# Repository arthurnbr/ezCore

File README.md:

# ezCore — porte-clés compagnon MeshCore (V3, circulaire, UX)

Compagnon MeshCore ultra-compact en **disque Ø48 mm** (type AirTag) autour du
**Seeed XIAO nRF52840** + module LoRa **Wio-SX1262** (EU868) : appairage BLE sans
code, mise à jour OTA par application, **antenne NFC ronde intégrée**, **LED
bi-couleur** de retour utilisateur, **port de charge/flash magnétique 4 points**
(pogo), et batterie **1050 mAh** au dos du boîtier.

> État : schéma ERC 0/0, PCB placée UX + routée (Freerouting). Quelques points DRC
> à finir dans KiCad. Tout est reproductible via `hardware/tools/`.

## Disposition UX (V3)

Placement pensé usage, carte propre et symétrique :

- **Pogo magnétique `J5` en haut** (VBUS/GND/D+/D−, type chargeur de montre) :
  charge + flash UF2 + série USB.
- **Bouton `SW1` + LED bi-couleur `D1`/`D2` à gauche** (90° du pogo) : retour
  visuel type AirPods (rouge = charge, vert = prêt, orange = transition). Pilotée
  par D9 (rouge) / D8 (vert) du XIAO via `R1`/`R2` (série).
- **Ports de debug SWD `TP1-TP4` sous le bouton** (RST / SWDIO / SWCLK / GND).
- **Interrupteur ON/OFF `SW3` à droite** (coupe la batterie).
- **XIAO `U1` + bobine NFC + Wio `U2` au centre**, pour un routage court.
- **Languette porte-clés en bas** (opposée au pogo) : contour avec repère de
  perçage en sérigraphie — tu perces toi-même, pas de trou dans le cuivre.
- **Repères de calage recto-verso** : traits de sérigraphie N/E/O en bord (plus de
  trous FID).

## Nouveautés V2 (vs V1 rectangulaire 26 × 52)

- **Forme circulaire Ø48 mm** + oreille porte-clés dédiée (trou NPTH, plus à
  travers la carte).
- **Module Wio-SX1262** placé en bord de disque, IPEX vers le pourtour :
  l'**antenne LoRa FPC s'enroule sur la paroi intérieure** du boîtier (~270°),
  à l'opposé de l'oreille et de l'antenne BLE du XIAO.
- **Port pogo 4 points** (`J5` = VBUS / GND / D+ / D−) : charge **et** flash UF2
  **et** série USB par le même connecteur magnétique, sans ouvrir le boîtier.
- **USB-C du XIAO non exposé** ; peut être **dessoudé** pour gagner de la place
  (le pogo fournit VBUS + D+/D− → le bootloader UF2 et l'OTA marchent quand même).
- **Batterie LPR604543** ronde Ø45 × 6 mm, 1050 mAh, PCM (keep-out circulaire sous
  la PCB).
- **Bobine NFC ronde** (Ø28, net-tie) centrée sous le XIAO.
- **Pas de pull-up SPI** : confirmé par le schéma Seeed de la carte d'extension
  (ses 3 résistances servent au connecteur 30-pin, à la LED et au bouton — pas au
  bus SPI du SX1262). Seul un **100 nF** (`C5`) de découplage est ajouté au VCC
  du module.

## Arborescence

```
meshtag/
├── README.md
├── docs/                     notes de conception
└── hardware/
    ├── MeshTag.kicad_pro      projet KiCad 9
    ├── MeshTag.kicad_sch      schéma (généré)
    ├── MeshTag.kicad_pcb      PCB 2 couches, disque Ø48 mm (généré + routé)
    ├── MeshTag.net            netlist exportée
    ├── MeshTag.kicad_dru      règles DRC (exemption net-tie bobine NFC)
    ├── sym-lib-table          → lib/MeshTag.kicad_sym (locale)
    ├── fp-lib-table           → lib/MeshTag.pretty (locale)
    ├── lib/
    │   ├── MeshTag.kicad_sym  TOUS les symboles (projet autonome)
    │   ├── MeshTag.pretty/    TOUTES les empreintes (projet autonome)
    │   └── 3dmodels/          modèles 3D STEP (constructeur / LCSC, alignés)
    ├── tools/
    │   ├── gen_sch.py         génère le schéma lisible (blocs + stubs + notes + champs BOM)
    │   ├── build_pcb.py       place les empreintes, dessine le contour, zones
    │   ├── route_pcb.sh       DSN → Freerouting → import SES → zones → DRC
    │   └── export_jlc.py      fichiers JLCPCB PCBA (gerbers zip, BOM, CPL)
    └── fab/
        ├── jlc/               MeshTag_gerbers.zip + MeshTag_BOM_JLC.csv + MeshTag_CPL_JLC.csv
        ├── gerbers/           Gerbers + perçage (Protel + gbrjob)
        ├── schematic.png      rendu du schéma
        ├── render_3d_top.png  rendu 3D
        └── BOM.csv            BOM complète (valeurs, LCSC, MPN, fabricant)
```

Toutes les bibliothèques (symboles, empreintes, **modèles 3D**) sont **copiées
dans le projet** (`${KIPRJMOD}/lib/3dmodels`) : rien ne dépend des bibliothèques
système. Provenance des modèles 3D :

| Empreinte | Modèle 3D | Source |
|---|---|---|
| `XIAO-nRF52840-SMD` | `XIAO-nRF52840-SMD.step` | STEP officiel Seeed (« XIAO-nRF52840 v3 », Printables Seeed Studio), recalé sur les pads 19–22 (écart < 0,01 mm) ; empreinte identique à la lib KiCad officielle Seeed `OPL_Kicad_Library` |
| `Wio-SX1262-Module` | `Wio-SX1262-Module.step` | LCSC/EasyEDA C55348741, recalé sur le WRL EasyEDA (écart 0,03 mm) ; pads identiques à EasyEDA à ±0,02 mm |
| `MagPogo_4P_P2.50mm_YZT0675` | `MagPogo_4P_P2.50mm_YZT0675.step` | LCSC/EasyEDA C5126846, recalé ; empreinte = EasyEDA + plan constructeur |
| `SW_Push_1P1T-SH_NO_CK_KMR2xxG` | idem `.step` | lib KiCad officielle (KMR2 avec patte de masse, cf. fiche C&K) |
| `SW_SPDT_PCM12` | idem `.step` | lib KiCad officielle (C&K PCM12) |
| `C_0402_1005Metric`, `R_0402` | idem `.step` | lib KiCad officielle |
| `LED_0402_Red_XL-1005SURC` / `LED_0402_Green_XL-1005UGC` | idem `.step` | LCSC/EasyEDA C25503345 / C965793, recalés |

Les empreintes sans 3D (bobine NFC, pastilles batterie, fiducials, test points)
sont du cuivre/pads, sans pièce physique.

Pour régénérer le schéma : `python3 tools/gen_sch.py` (ERC 0/0).

## Fabrication JLCPCB (PCBA)

```bash
cd hardware && python3 tools/export_jlc.py   # → fab/jlc/
```

JLC pose les **12 composants CMS/THT** du tableau ci-dessous ; **U1 (XIAO) et U2
(Wio-SX1262) ne sont pas assemblés** : pas de champ `LCSC`, et « exclu de la BOM /
des fichiers de placement » sur le PCB → absents de la BOM et du CPL JLC, soudés à
la main. Ils ne sont **pas** marqués DNP pour que leur modèle 3D reste visible
(KiCad masque le 3D des composants DNP). Les champs `LCSC` / `MPN` /
`Manufacturer` sont dans le schéma.

| Réf | Valeur | LCSC | MPN | Type JLC |
|---|---|---|---|---|
| C1 | 10 µF 6,3 V X5R 0402 | C15525 | Samsung CL05A106MQ5NUNC | base |
| C2, C5 | 100 nF 16 V X7R 0402 | C1525 | Samsung CL05B104KO5NNNC | base |
| C3, C4 | 47 pF 50 V C0G 0402 (accord NFC, à confirmer au VNA) | C1567 | FH 0402CG470J500NT | base |
| R1, R2 | 470 Ω 1 % 0402 | C25117 | UNI-ROYAL 0402WGF4700TCE | base |
| D1 | LED rouge 0402 | C25503345 | XINGLIGHT XL-1005SURC | étendu |
| D2 | LED verte 0402 | C965793 | XINGLIGHT XL-1005UGC | étendu |
| SW1 | bouton KMR2 2 N | C72443 | C&K KMR221GLFS | étendu |
| SW3 | interrupteur coulissant 0,3 A | C221841 | C&K PCM12SMTR | étendu |
| J5 | réceptacle pogo magnétique 4P pas 2,5 mm | C5126846 | Xinyangze YZT0675-20048-04025-01 | étendu |

## Régénérer le PCB

```bash
cd hardware
export KIPRJMOD="$PWD"
kicad-cli sch export netlist --format kicadsexpr -o MeshTag.net MeshTag.kicad_sch
python3 tools/build_pcb.py        # place + contour + zoneinfo
bash   tools/route_pcb.sh         # autoroute + zones + DRC
```

Dépendances : KiCad 9 (`kicad-cli`, module `pcbnew`), Freerouting 2.5
(`FREEROUTING_JAR`, défaut `/tmp/tools/freerouting.jar`) exécuté avec un JRE ≥ 23
(`JAVA25`, défaut `/usr/lib/jvm/java-25-openjdk-amd64/bin/java`).

## Architecture électrique

Brochage choisi pour le routage (XIAO pads 1→7 en face des broches Wio
6,5,4,3,2,1,11). **Diffère de la variante MeshCore `xiao_nrf52`** : il faut un env
PlatformIO dédié (flags `P_LORA_*`, `SX126X_RXEN`, `PIN_USER_BTN`, `P_LORA_TX_LED`,
I2C désactivé) et une copie de `variant.h` (`PIN_SPI_*` y sont codés en dur).

| Signal          | Broche Wio | Pad XIAO | Broche XIAO | GPIO nRF | Net       |
|-----------------|------------|----------|-------------|----------|-----------|
| NSS             | 6          | 1        | D0          | P0.02    | LORA_NSS  |
| NRST            | 5          | 2        | D1          | P0.03    | LORA_RST  |
| SCK             | 4          | 3        | D2          | P0.28    | SPI_SCK   |
| MOSI            | 3          | 4        | D3          | P0.29    | SPI_MOSI  |
| MISO            | 2          | 5        | D4          | P0.04    | SPI_MISO  |
| RF_SW / RXEN    | 1          | 6        | D5          | P0.05    | LORA_RXEN |
| BUSY            | 11         | 7        | D6          | P1.11    | LORA_BUSY |
| DIO1            | 12         | 11       | D10         | P1.15    | LORA_DIO1 |
| Bouton `SW1`    | —          | 8        | D7          | P1.12    | BTN       |
| LED verte       | —          | 9        | D8          | P1.13    | via R2    |
| LED rouge       | —          | 10       | D9          | P1.14    | via R1    |

- **U1** XIAO nRF52840 (CMS à plat, castellations), face avant.
- **U2** module Wio-SX1262 nu (IPEX), face avant, au-dessus du XIAO.
- **AE1** bobine NFC 2 couches (net-tie NFC1/NFC2) pour l'appairage par approche.
- **C1/C2** découplage 3V3, **C3/C4** accord NFC, **C5** découplage Wio — tous en
  **0402** (petits). **D1/D2** LED bi-couleur 0402 + **R1/R2** résistances 0402.
  Tous les symboles ont leur **footprint assigné** (mise à jour schéma → PCB OK).
- **SW1** bouton utilisateur ; **SW3** interrupteur de coupure batterie **côté
  masse** : BAT+ reste sur `VBATT`, SW3 relie/coupe BAT− (`BAT_N`) de `GND`.
- **BT1** pastilles fils LiPo 1S ; **TP1-4** RST_MCU / SWDIO / SWCLK / GND.
- Plan de masse coulé sur les deux faces (zone médiane).
- **Keep-out antenne BLE** : pas de cuivre sous l'antenne 2,4 GHz intégrée du XIAO.
- **Keep-out bobine NFC** : pas de plan de masse dans la bande basse.

L'**antenne LoRa** n'est pas sur la PCB : elle se branche sur l'IPEX du module
Wio (FPC 868 MHz, voir `docs/`).

## Accord de la bobine NFC

Bobine **ronde** 6 tours/couche (Ø15 mm), ~1,5–2 µH estimés, centrée sous le XIAO.
**La valeur exacte doit être mesurée au NanoVNA** puis les condensateurs C3/C4
choisis entre 33 et 150 pF (C0G 0402) pour résonner à 13,56 MHz — procédure
standard (wiki Seeed XIAO NFC).

## Alimentation, charge et empilage (stack)

**Tous les composants sont sur la face AVANT** (gravure simple face pour les
pièces). La face avant porte aussi la **bobine NFC** (surface de tap). La
**batterie occupe seule l'arrière**, dans le boîtier.

```
[ téléphone ]
  bobine NFC          face AVANT du PCB (cuivre vers le téléphone)
  PCB  (XIAO, Wio, pogo, switch, bouton, caps, TP sur l'avant)
  --- film ferrite 0,1 mm ---   <-- indispensable pour le NFC
  BATTERIE Ø45 1050 mAh         collée au dos, dans le boîtier
[ dos du boîtier ]
```

- **Batterie** : LPR604543 ronde Ø45 × 6 mm, 1050 mAh, PCM ; fils soudés sur les
  pastilles `BT1` (BAT+/BAT−). Elle n'a **pas** de modèle 3D sur la PCB (ce n'est
  pas un composant CMS). Le chargeur BQ25101 du XIAO charge à 50/100 mA.
- **Film ferrite 0,1 mm** entre la bobine et la batterie : **obligatoire**. Le PCB
  (FR4) est transparent au champ magnétique et ne protège pas ; sans ferrite,
  l'enveloppe aluminium de la batterie absorbe le champ et tue le NFC. ~2 €.
- **Port pogo magnétique `J5`** (Xinyangze YZT0675, 4P pas 2,50 mm, contacts plats +
  2 aimants) : VBUS/GND/D+/D− → charge + flash UF2 + série USB. Le câble doit être
  un **mâle à ressorts 4P au pas de 2,5 mm** avec le **même ordre de broches** et
  des aimants de polarité opposée (sinon VBUS/GND s'inversent).
- **USB-C du XIAO** non exposé ; dessoudage optionnel pour gagner de la hauteur.
  Les pogo D+/D− se câblent alors sur les pads USB du XIAO (`TP5`/`TP6`).

## État du routage (à finir dans la GUI KiCad)

Le disque est **placé** (0 conflit de pastilles), les plans GND coulés, mais
l'auto-routeur ne boucle pas tout sur 2 couches à cette densité. **~13 liaisons
courtes restent à tirer à la main** (SPI LoRa U1↔U2, NFC, VBATT, RST) — ~15 min
dans KiCad, en passant par la face arrière là où le plan GND laisse la place.

## Limitations connues (à finir dans la GUI KiCad)

- **~13 nets non routés** (voir ci-dessus) : SPI LoRa, NFC1/NFC2, VBATT, RST_MCU.
- **Ratsnest bobine NFC** : la spirale est du cuivre d'empreinte (net-tie) ;
  KiCad peut la signaler « non connectée » alors qu'elle est physiquement continue.
- **`solder_mask_bridge`** entre pastilles castellées serrées du XIAO : cosmétique,
  accepté par les fabricants (ponts de masque tolérés sur ce module).
- Antenne LoRa, batterie et boîtier : voir `docs/bom_v2.md`.

## Fabrication maison (photogravure UV, double face)

Règles de conception adaptées à la **photogravure UV maison**, pas à un fab pro :

| Paramètre | Valeur |
|---|---|
| Couches | 2 (F.Cu + B.Cu uniquement) |
| Largeur de piste | **0,3 mm** |
| Isolation | **0,3 mm** |
| Vias | **⌀1,0 mm pad / perçage 0,6 mm** — métallisés à la main (rivet ou fil soudé des deux côtés) |
| Calage recto-verso | 3 repères `FID1/2/3` (trous ⌀0,6) en triangle : percer puis aligner les deux films dessus |

**Procédure vias maison** : chaque via se perce à 0,6 mm puis se métallise avec un
rivet à œillet ou un bout de fil soudé sur les deux faces. Il faut donc router en
gardant les vias **hors des composants** (soudables des deux côtés).

> ⚠️ **Via central de la bobine NFC** : il tombe sous le XIAO. Le riveter/souder
> **avant** de poser le XIAO, ou déplacer la bobine `AE1` dans la zone libre en bas
> du disque si l'accès est requis après assemblage.

# ezCore

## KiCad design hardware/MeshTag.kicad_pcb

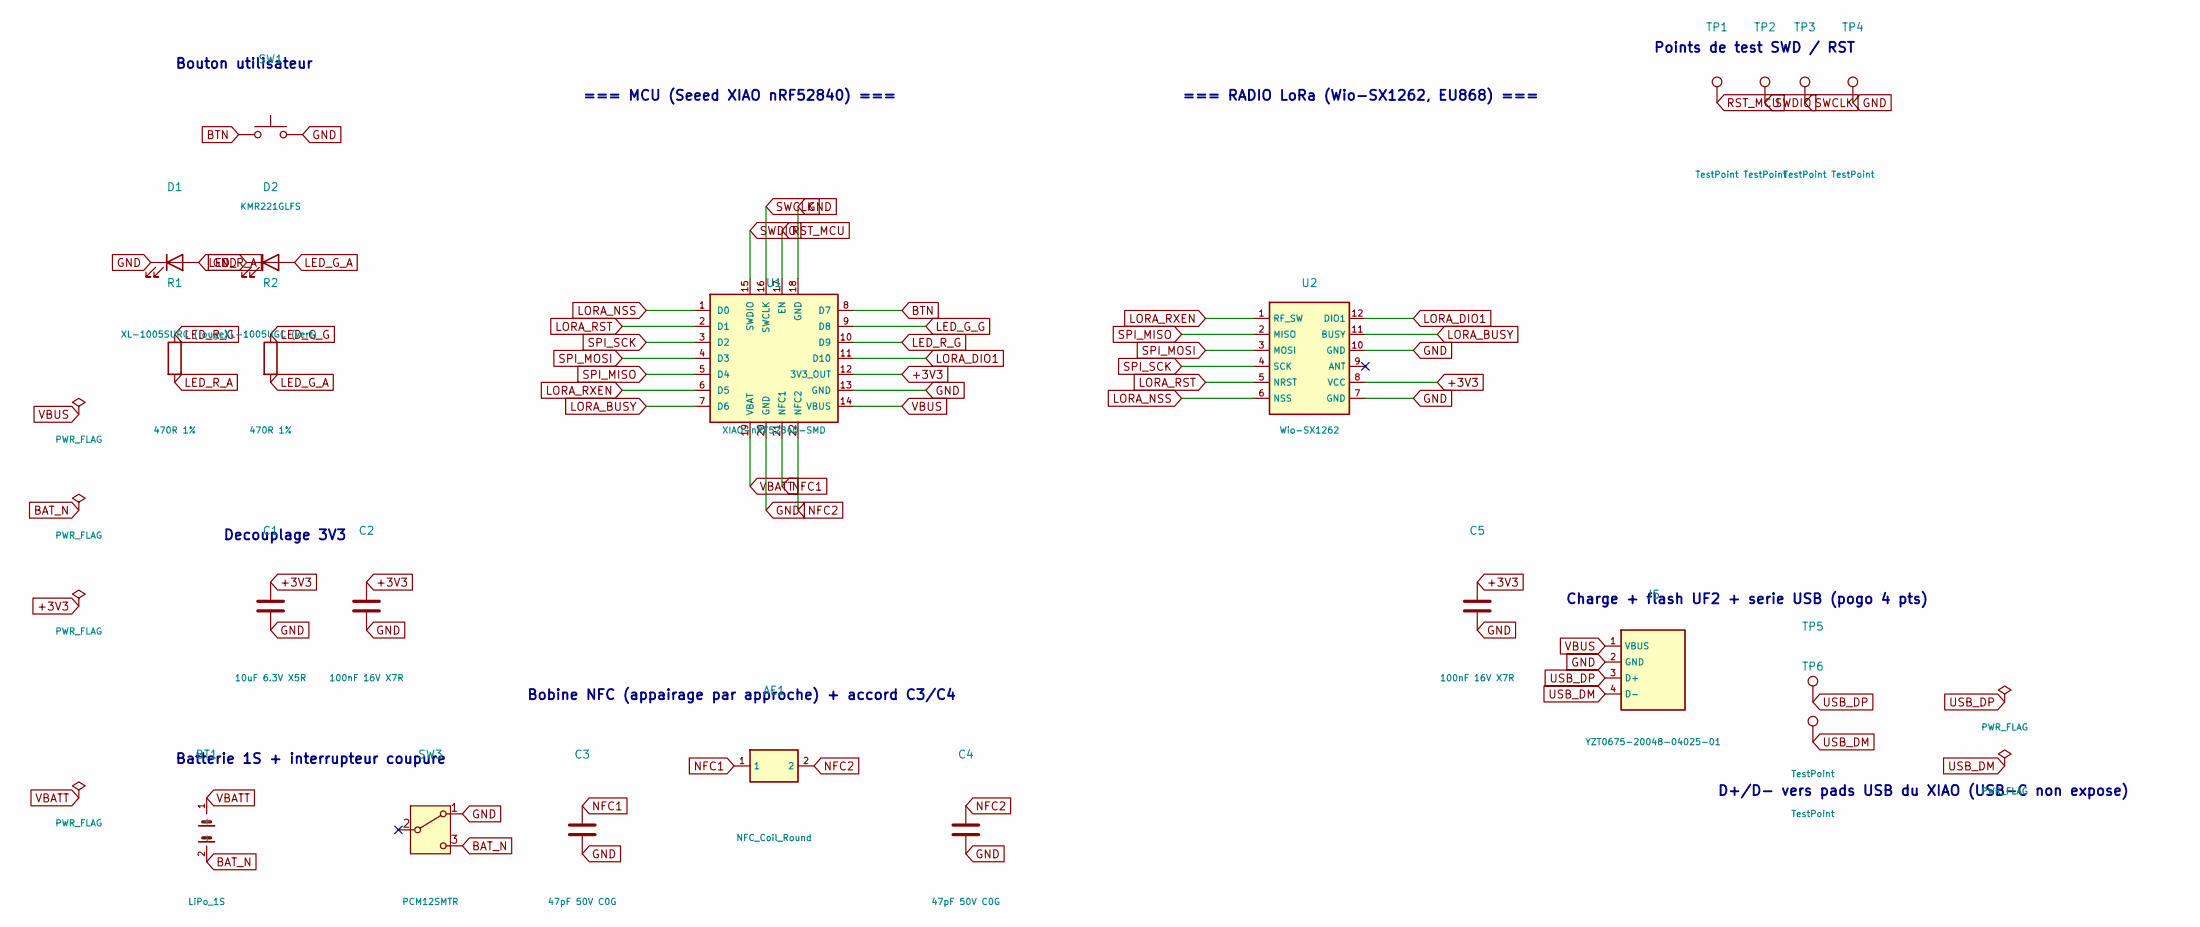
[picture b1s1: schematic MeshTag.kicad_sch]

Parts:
AE1: NFC_Coil_Round
BT1: LiPo_1S; Batt_WirePads_2x
C1: 10uF 6.3V X5R; C_0402_1005Metric; MPN CL05A106MQ5NUNC; LCSC C15525
C2, C5: 100nF 16V X7R; C_0402_1005Metric; MPN CL05B104KO5NNNC; LCSC C1525
C3, C4: 47pF 50V C0G; C_0402_1005Metric; MPN 0402CG470J500NT; LCSC C1567
D1: XL-1005SURC (rouge); LED_0402_Red_XL-1005SURC; MPN XL-1005SURC; LCSC C25503345
D2: XL-1005UGC (vert); LED_0402_Green_XL-1005UGC; MPN XL-1005UGC; LCSC C965793
J5: YZT0675-20048-04025-01; MagPogo_4P_P2.50mm_YZT0675; MPN YZT0675-20048-04025-01; LCSC C5126846
R1, R2: 470R 1%; R_0402; MPN 0402WGF4700TCE; LCSC C25117
SW1: KMR221GLFS; SW_Push_1P1T-SH_NO_CK_KMR2xxG; MPN KMR221GLFS; LCSC C72443
SW3: PCM12SMTR; SW_SPDT_PCM12; MPN PCM12SMTR; LCSC C221841
TP1, TP2, TP3, TP4, TP5, TP6: TestPoint; TestPoint_Pad_1.0x1.0mm
U1: XIAO-nRF52840-SMD; MPN 102010448; JLC Non assemblé par JLC - soudé à la main
U2: Wio-SX1262; Wio-SX1262-Module; MPN 114993390; JLC Non assemblé par JLC - soudé à la main

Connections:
+3V3: C1.1, C2.1, C5.1, U1.12 (3V3_OUT), U2.8 (VCC)
BAT_N: BT1.2 (-), SW3.3 (C)
BTN: SW1.1, U1.8 (D7)
GND: C1.2, C2.2, C3.2, C4.2, C5.2, D1.1 (K), D2.1 (K), J5.2 (GND), SW1.2, SW3.1 (A), TP4.1, U1.13 (GND), U1.18 (GND), U1.20 (GND), U2.7 (GND), U2.10 (GND)
LED_G_A: D2.2 (A), R2.2
LED_G_G: R2.1, U1.9 (D8)
LED_R_A: D1.2 (A), R1.2
LED_R_G: R1.1, U1.10 (D9)
LORA_BUSY: U1.7 (D6), U2.11 (BUSY)
LORA_DIO1: U1.11 (D10), U2.12 (DIO1)
LORA_NSS: U1.1 (D0), U2.6 (NSS)
LORA_RST: U1.2 (D1), U2.5 (NRST)
LORA_RXEN: U1.6 (D5), U2.1 (RF_SW)
NFC1: AE1.1, C3.1, U1.21 (NFC1)
NFC2: AE1.2, C4.1, U1.22 (NFC2)
RST_MCU: TP1.1, U1.17 (EN)
SPI_MISO: U1.5 (D4), U2.2 (MISO)
SPI_MOSI: U1.4 (D3), U2.3 (MOSI)
SPI_SCK: U1.3 (D2), U2.4 (SCK)
SWCLK: TP3.1, U1.16 (SWCLK)
SWDIO: TP2.1, U1.15 (SWDIO)
USB_DM: J5.4 (D-), TP6.1
USB_DP: J5.3 (D+), TP5.1
VBATT: BT1.1 (+), U1.19 (VBAT)
VBUS: J5.1 (VBUS), U1.14 (VBUS)

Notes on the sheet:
Decouplage 3V3
Points de test SWD / RST
Batterie 1S + interrupteur coupure
=== RADIO LoRa (Wio-SX1262, EU868) ===
D+/D- vers pads USB du XIAO (USB-C non expose)
=== MCU (Seeed XIAO nRF52840) ===
Bouton utilisateur
Bobine NFC (appairage par approche) + accord C3/C4
Charge + flash UF2 + serie USB (pogo 4 pts)

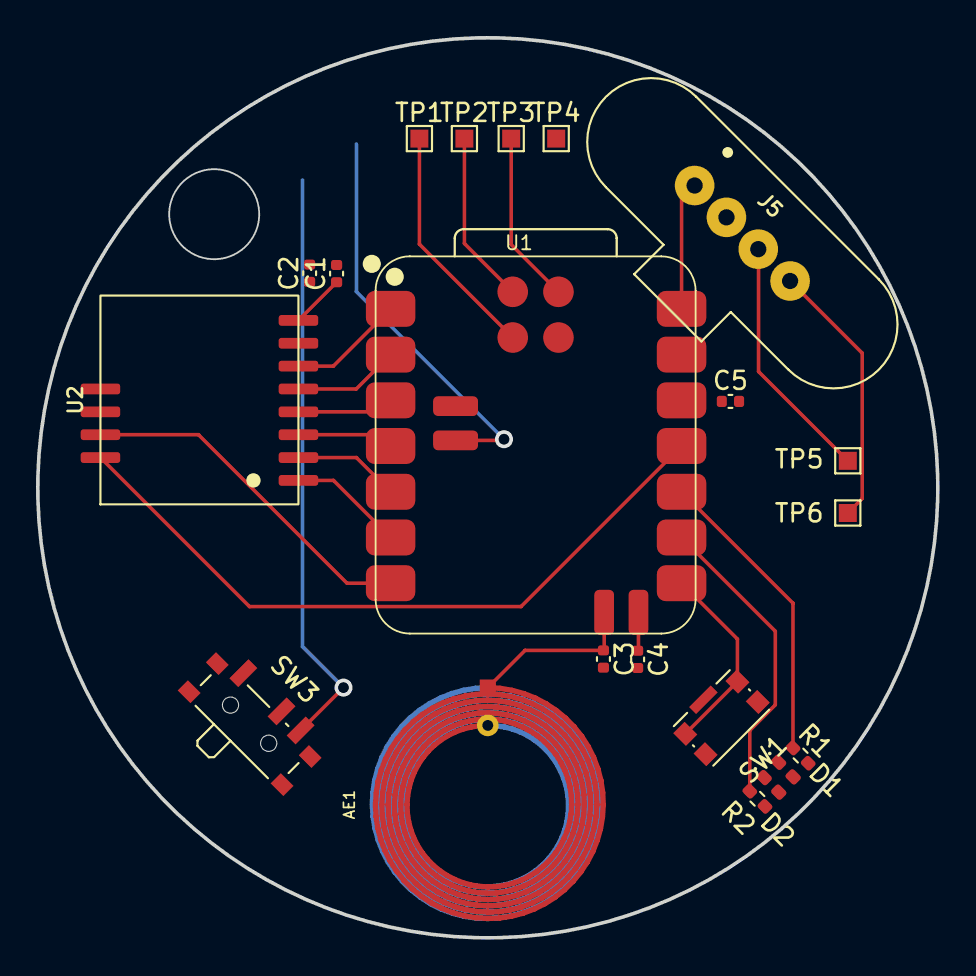
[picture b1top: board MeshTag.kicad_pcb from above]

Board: 2 copper layers, 50.0 x 50.0 mm, 22 parts (1 on the bottom side), 25 nets.
